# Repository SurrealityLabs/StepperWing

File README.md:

# StepperWing
FeatherWing board for driving 4x 28BYJ-48 stepper motors

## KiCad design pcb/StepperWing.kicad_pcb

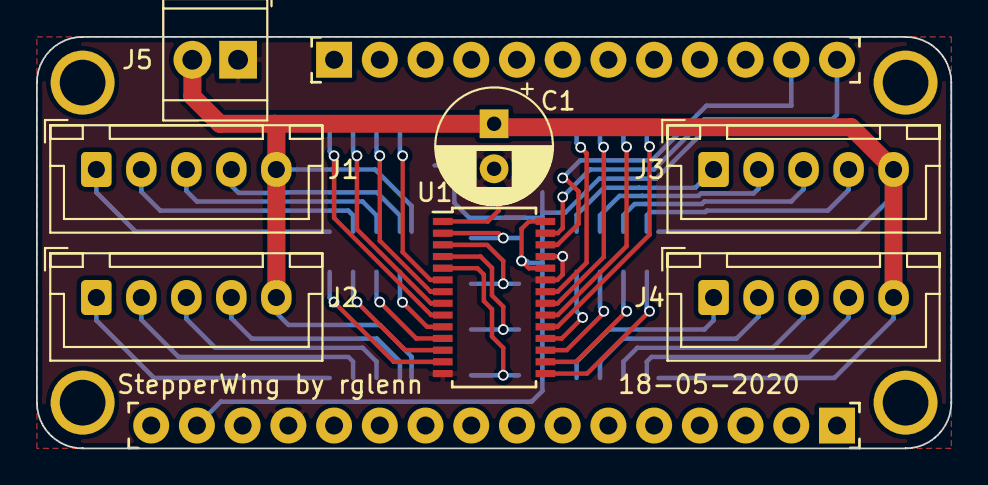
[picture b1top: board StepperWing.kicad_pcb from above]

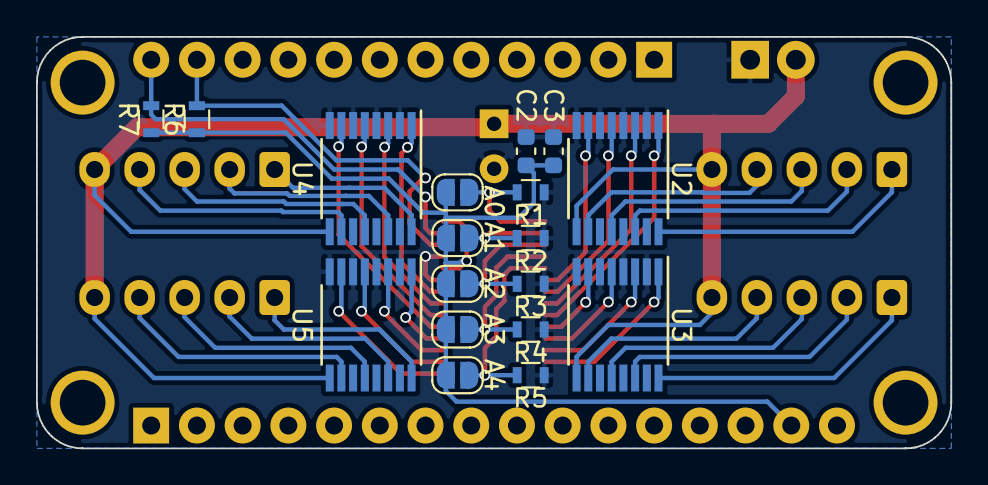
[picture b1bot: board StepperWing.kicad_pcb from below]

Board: 2 copper layers, 50.8 x 22.9 mm, 28 parts (18 on the bottom side), 42 nets.

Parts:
A0, A1, A2, A3, A4: SolderJumper_2_Open; SolderJumper-2_P1.3mm_Open_RoundedPad1.0x1.5mm
C1: 100u; CP_Radial_D6.3mm_P2.50mm
C2: 100n; C_0603_1608Metric
C3: 1u; C_0603_1608Metric
J1, J2, J3, J4: Conn_01x05; JST_XH_B5B-XH-A_1x05_P2.50mm_Vertical
J5: Conn_01x02; TerminalBlock_TE_282834-2_1x02_P2.54mm_Horizontal
JP1: PinHeader_01x16_2.54mm; Conn_PinHeader_1x16
JP3: PinHeader_01x12_2.54mm; Conn_PinHeader_1x12
PCB**: VAL**; PCB_FeatherWing
R1, R2, R3, R4, R5, R6, R7: 10K; R_0603
U1: PCA9685PW; TSSOP-28_4.4x9.7mm_P0.65mm
U2, U3, U4, U5: ULN2003A; TSSOP-16_4.4x5mm_Pitch0.65mm

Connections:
+5V: C1.1, J1.5, J2.5, J3.5, J4.5, J5.2, U2.9, U3.9, U4.9, U5.9
/MOTOR1_A: U1.9, U2.1
/MOTOR1_B: U1.8, U2.3
/MOTOR1_C: U1.7, U2.5
/MOTOR1_D: U1.6, U2.7
/MOTOR2_A: U1.22, U4.1
/MOTOR2_B: U1.21, U4.3
/MOTOR2_C: U1.20, U4.5
/MOTOR2_D: U1.19, U4.7
/MOTOR3_A: U1.13, U3.1
/MOTOR3_B: U1.12, U3.3
/MOTOR3_C: U1.11, U3.5
/MOTOR3_D: U1.10, U3.7
/MOTOR4_A: U1.18, U5.1
/MOTOR4_B: U1.17, U5.3
/MOTOR4_C: U1.16, U5.5
/MOTOR4_D: U1.15, U5.7
/SCL: JP3.11, R6.2, U1.26
/SDA: JP3.12, R7.2, U1.27
GND: C1.2, C2.2, C3.2, J5.1, JP1.13, R1.2, R2.2, R3.2, R4.2, R5.2, U1.14, U1.23, U1.25, U2.2, U2.4, U2.6, U2.8, U3.2, U3.4, U3.6, U3.8, U4.2, U4.4, U4.6, U4.8, U5.2, U5.4, U5.6, U5.8
unnamed: A0.1, R1.1, U1.1
unnamed: A1.1, R2.1, U1.2
unnamed: A2.1, R3.1, U1.3
unnamed: A3.1, R4.1, U1.4
unnamed: A4.1, R5.1, U1.5
unnamed: J1.1, U2.16
unnamed: J1.2, U2.14
unnamed: J1.3, U2.12
unnamed: J1.4, U2.10
unnamed: J2.1, U3.16
unnamed: J2.2, U3.14
unnamed: J2.3, U3.12
unnamed: J2.4, U3.10
unnamed: J3.1, U4.16
unnamed: J3.2, U4.14
unnamed: J3.3, U4.12
unnamed: J3.4, U4.10
unnamed: J4.1, U5.16
unnamed: J4.2, U5.14
unnamed: J4.3, U5.12
unnamed: J4.4, U5.10
VCC: A0.2, A1.2, A2.2, A3.2, A4.2, C2.1, C3.1, JP1.15, R6.1, R7.1, U1.24, U1.28

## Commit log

2020-05-18 Adding first rev of PCB
